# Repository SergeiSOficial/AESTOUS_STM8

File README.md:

# AESTOUS_STM8
Open source thermostat AESTOUS based on cheap stm8s003

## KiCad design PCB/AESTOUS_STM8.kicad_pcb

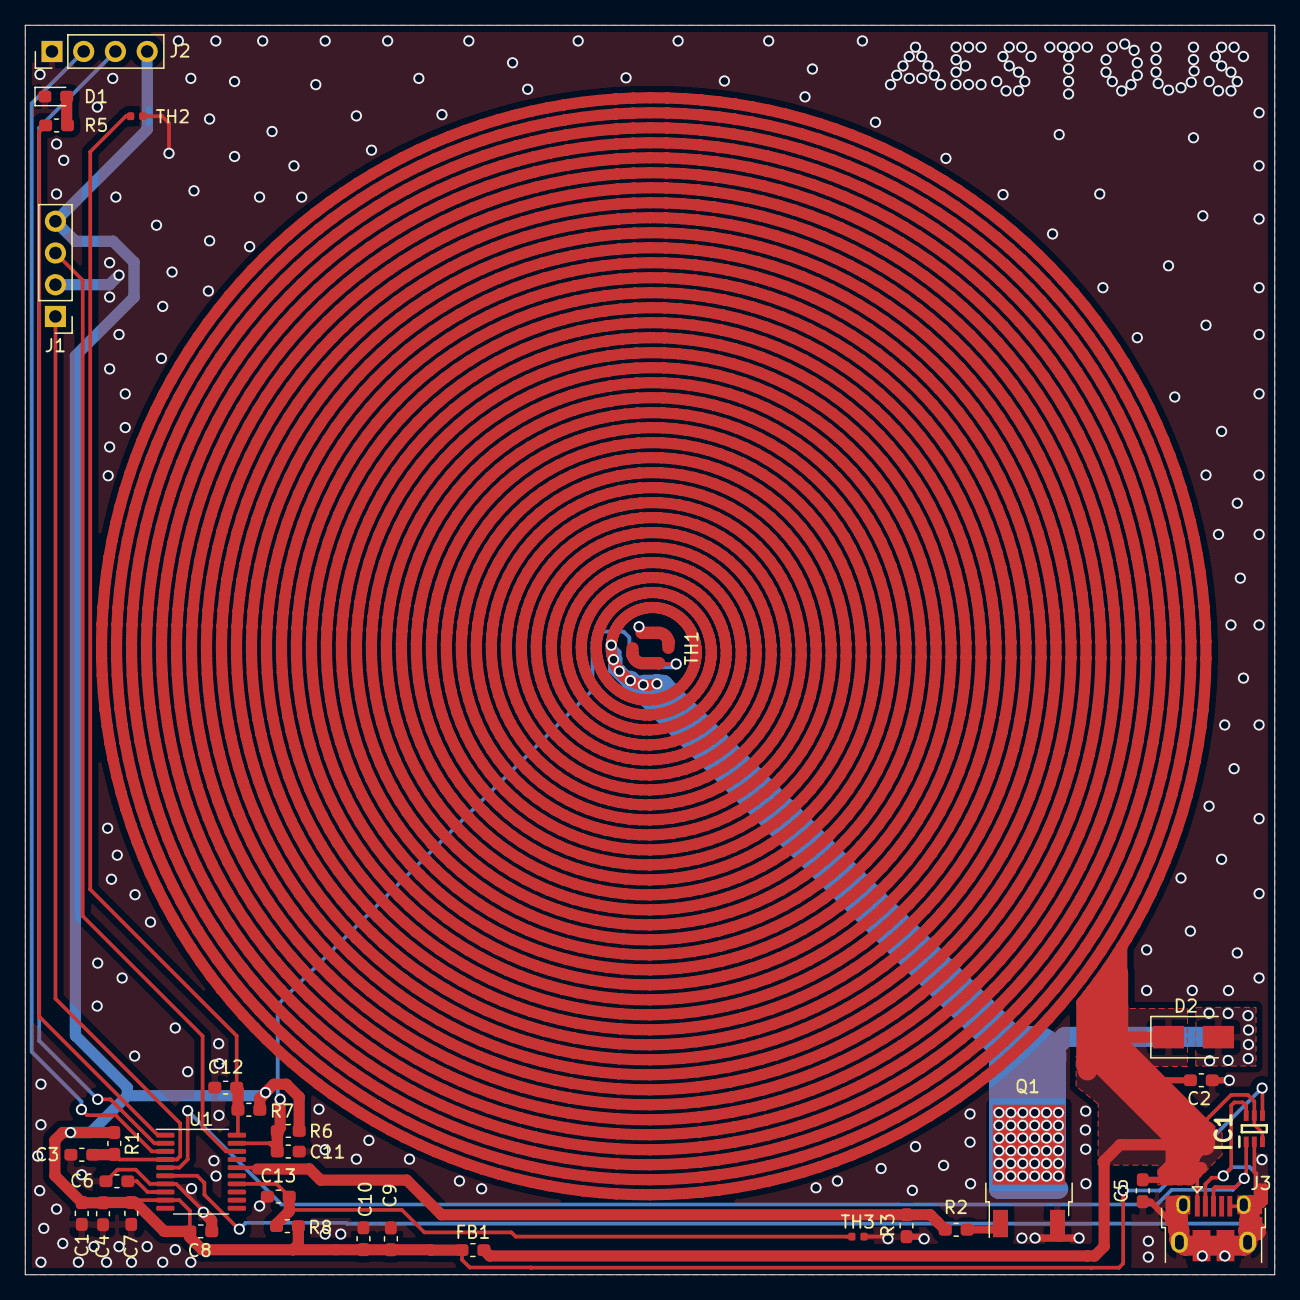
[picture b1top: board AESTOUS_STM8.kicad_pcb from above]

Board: 2 copper layers, 100.0 x 100.0 mm, 32 parts (0 on the bottom side), 17 nets.

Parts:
C1, C2, C3, C4, C5, C6, C8, C9, C10, C11, C12, C13: 1UF 50V; C_0603_1608Metric_Pad1.05x0.95mm_HandSolder
C7: 100PF 50V; C_0603_1608Metric_Pad1.05x0.95mm_HandSolder
D1: KT-0603R; LED_0603_1608Metric_Pad1.05x0.95mm_HandSolder
D2: SS34; D_SMA
FB1: BLM18AG102SN1D; L_0603_1608Metric_Pad1.05x0.95mm_HandSolder
IC1: SMF05CT1G; SOT65P210X110-6N
J1, J2: Conn_01x04; PinHeader_1x04_P2.54mm_Vertical
J3: USB_B_Micro; USB_Micro-B_Amphenol_10103594-0001LF_Horizontal
Q1: NCE2060K; TO-252-2
R1, R6, R7, R8: 10 KOHMS ±1%; R_0603_1608Metric_Pad1.05x0.95mm_HandSolder
R2: 270 OHMS ±1%; R_0603_1608Metric_Pad1.05x0.95mm_HandSolder
R3: 30 KOHMS ±1%; R_0603_1608Metric_Pad1.05x0.95mm_HandSolder
R5: 330 OHMS ±1%; R_0603_1608Metric_Pad1.05x0.95mm_HandSolder
TH1: NTC 10KOHMS ±1%; 0403_inside
TH2, TH3: NTC 10KOHMS ±1%; R_0402_1005Metric
U1: STM8S003F3P; TSSOP-20_4.4x6.5mm_P0.65mm

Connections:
0: C1.2, C2.2, C3.2, C4.2, C5.2, C6.2, C7.2, C8.2, C9.2, C10.2, C11.2, C12.2, C13.2, D1.1, IC1.2, J1.2, J2.1, J3.5, J3.6, Q1.3, R3.1, TH1.1, TH2.2, TH3.2, U1.7
+5VD: C1.1, C4.1, C7.1, C8.1, C9.1, C10.1, FB1.1, IC1.4, J1.4, J2.4, R1.1, R6.1, R7.1, R8.1, U1.9
/ADC_IN2: C13.1, R8.2, TH3.1, U1.14
/ADC_IN3: C11.1, R6.2, TH1.2, U1.19
/ADC_IN4: C12.1, R7.2, TH2.1, U1.20
/DM: IC1.6, J3.2, U1.6
/DP: IC1.1, J3.3, U1.5
/LED: R5.1, U1.1
/NRST: C3.1, J1.1, R1.2, U1.4
/SWIM: J1.3, U1.18
/TIM1_CH1: R2.2, R3.2, U1.16
/UART_RX: J2.2, U1.3
/UART_TX: J2.3, U1.2
unnamed: C6.1, U1.8
unnamed: D1.2, R5.2
unnamed: Q1.1, R2.1
VDD: C2.1, C5.1, D2.1, D2.2, FB1.2, IC1.3, IC1.5, J3.1, Q1.2

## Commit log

2020-08-01 Fisrt init commit
2020-08-01 Added pcb schematic
2020-11-04 new version
2020-11-25 Add iar project and update PCB
2020-11-25 update gitignore
2020-11-25 update gitignore 2
2020-11-25 try to fix gitignore
2020-11-28 update gitignore and project file
2020-11-28 remove ignored files
2020-11-29 First integrate code from old project
2020-11-29 Tune for hardware
2020-11-29 try to change and debug target
2020-12-06 Change configuration and working simple loop
2020-12-13 turn on adc measurement
